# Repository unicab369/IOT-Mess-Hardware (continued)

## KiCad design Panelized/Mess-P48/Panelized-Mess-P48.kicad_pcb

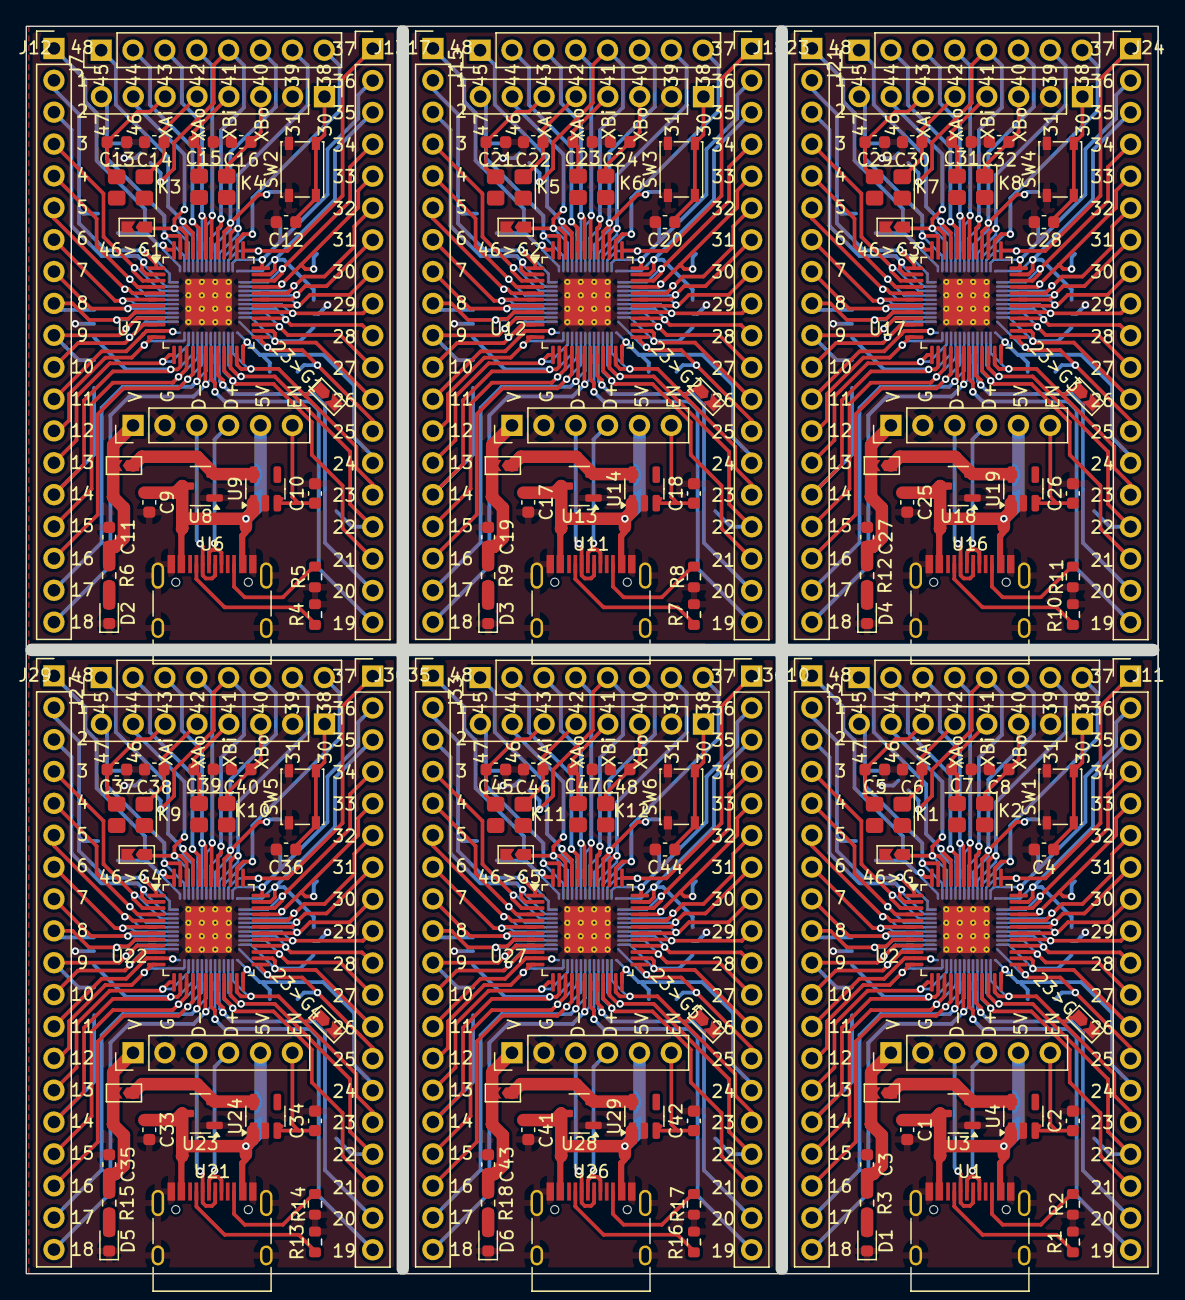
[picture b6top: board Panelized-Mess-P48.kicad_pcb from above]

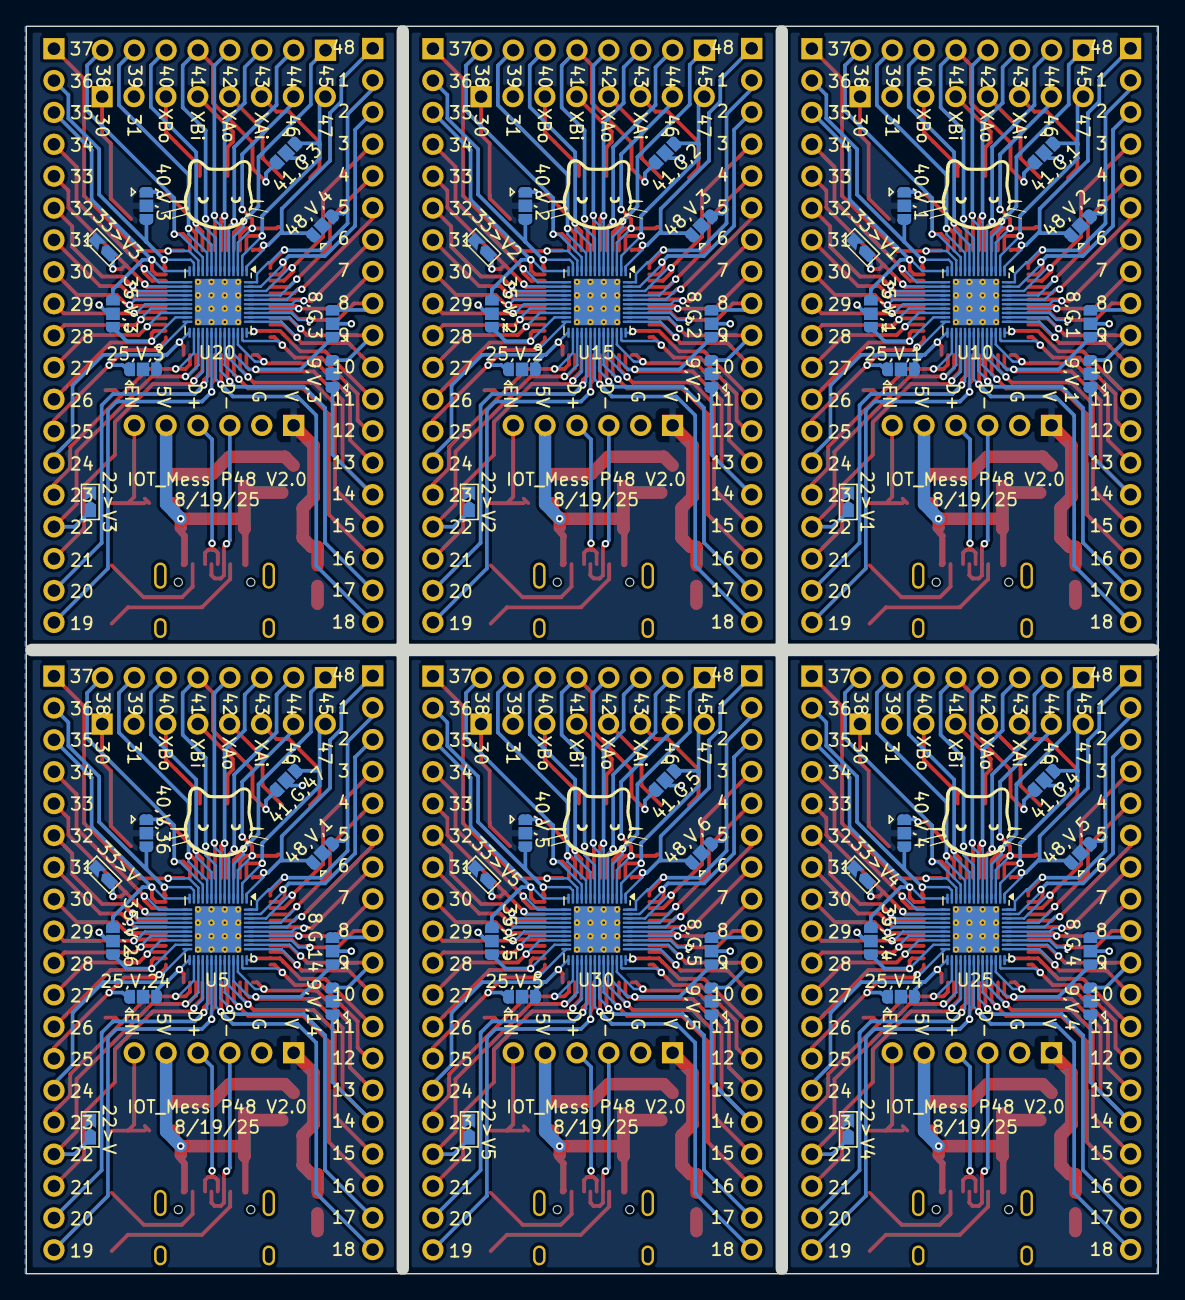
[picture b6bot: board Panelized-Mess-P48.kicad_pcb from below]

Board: 2 copper layers, 90.2 x 99.4 mm, 222 parts (60 on the bottom side), 63 nets.

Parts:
8,G,1, 8,G,2, 8,G,3, 8,G,4, 8,G,5, 8,G,14, 9,V,1, 9,V,2, 9,V,3, 9,V,4, 9,V,5, 9,V,14, 25,V,1, 25,V,2, 25,V,3, 25,V,4, 25,V,5, 25,V,24, 35,V,1, 35,V,2, 35,V,3, 35,V,4, 35,V,5, 35,V,26, 40,V,1, 40,V,2, 40,V,3, 40,V,4, 40,V,5, 40,V,36, 41,G,1, 41,G,2, 41,G,3, 41,G,4, 41,G,5, 41,G,47, 48,V,1, 48,V,2, 48,V,3, 48,V,4, 48,V,5, 48,V,6: Jumper; Jumper-3_P1.3mm_Open_RoundedPad1.0x1.5mm
22>V, 22>V1, 22>V2, 22>V3, 22>V4, 22>V5, 23>G, 23>G1, 23>G2, 23>G3, 23>G4, 23>G5, 33>V, 33>V1, 33>V2, 33>V3, 33>V4, 33>V5, 46>G, 46>G1, 46>G2, 46>G3, 46>G4, 46>G5: Jumper_2; Jumpper-triangle
C1, C9, C17, C25, C33, C41: 10u; C_0603_1608Metric
C2, C3, C10, C11, C18, C19, C26, C27, C34, C35, C42, C43: 1u; C_0603_1608Metric
C4, C12, C20, C28, C36, C44: .1u; C_0603_1608Metric
C5, C6, C13, C14, C21, C22, C29, C30, C37, C38, C45, C46: 15-30pF; C_0603_1608Metric
C7, C8, C15, C16, C23, C24, C31, C32, C39, C40, C47, C48: 12-25pF; C_0603_1608Metric
D1, D2, D3, D4, D5, D6: LED; LED_0603_1608Metric
J1, J5, J9, J19, J25, J31: Jumper_2; Jumpper-triangle
J2, J6, J14, J20, J26, J32: Conn_01x06_Pin; PinHeader_1x06_P2.54mm_Vertical
J3, J4, J7, J8, J15, J16, J21, J22, J27, J28, J33, J34: Conn_01x08_Pin; PinHeader_1x08_P2.54mm_Vertical
J10, J11, J12, J13, J17, J18, J23, J24, J29, J30, J35, J36: Conn_01x19_Pin; PinHeader_1x19_P2.54mm_Vertical
K1, K2, K3, K4, K5, K6, K7, K8, K9, K10, K11, K12: Crystal; Crystal_SMD_3225-4Pin_3.2x2.5mm
R1, R2, R4, R5, R7, R8, R10, R11, R13, R14, R16, R17: 5.1K; R_0603_1608Metric
R3, R6, R9, R12, R15, R18: R; R_0603_1608Metric
SW1, SW2, SW3, SW4, SW5, SW6: SW_Push; SW_SPST_PTS810
U1, U6, U11, U16, U21, U26: USB_C_Receptacle_USB2.0_16P; USB_C_Receptacle_HRO_TYPE-C-31-M-12
U2, U7, U12, U17, U22, U27: LQFP-48-1EP_7x7mm_P0.5mm_EP3.6x3.6mm
U3, U8, U13, U18, U23, U28: XC6206PxxxMR; SOT-23-3
U4, U9, U14, U19, U24, U29: ME6211C33M5; SOT-23-5
U5, U10, U15, U20, U25, U30: CH32L103C8T6; QFN-48-1EP_5x5mm_P0.35mm_EP3.7x3.7mm_ThermalVias

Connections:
5V: C1.1, C9.1, C17.1, C25.1, C33.1, C41.1, J2.5, J6.5, J14.5, J20.5, J26.5, J32.5, U1.A4 (VBUS), U1.A9 (VBUS), U1.B4 (VBUS), U1.B9 (VBUS), U3.3 (VI), U4.1 (V_{IN}), U6.A4 (VBUS), U6.A9 (VBUS), U6.B4 (VBUS), U6.B9 (VBUS), U8.3 (VI), U9.1 (V_{IN}), U11.A4 (VBUS), U11.A9 (VBUS), U11.B4 (VBUS), U11.B9 (VBUS), U13.3 (VI), U14.1 (V_{IN}), U16.A4 (VBUS), U16.A9 (VBUS), U16.B4 (VBUS), U16.B9 (VBUS), U18.3 (VI), U19.1 (V_{IN}), U21.A4 (VBUS), U21.A9 (VBUS), U21.B4 (VBUS), U21.B9 (VBUS), U23.3 (VI), U24.1 (V_{IN}), U26.A4 (VBUS), U26.A9 (VBUS), U26.B4 (VBUS), U26.B9 (VBUS), U28.3 (VI), U29.1 (V_{IN})
D+: J2.4, J6.4, J14.4, J20.4, J26.4, J32.4, U1.A6 (D+), U1.B6 (D+), U6.A6 (D+), U6.B6 (D+), U11.A6 (D+), U11.B6 (D+), U16.A6 (D+), U16.B6 (D+), U21.A6 (D+), U21.B6 (D+), U26.A6 (D+), U26.B6 (D+)
D-: J2.3, J6.3, J14.3, J20.3, J26.3, J32.3, U1.A7 (D-), U1.B7 (D-), U6.A7 (D-), U6.B7 (D-), U11.A7 (D-), U11.B7 (D-), U16.A7 (D-), U16.B7 (D-), U21.A7 (D-), U21.B7 (D-), U26.A7 (D-), U26.B7 (D-)
EN: C2.1, C10.1, C18.1, C26.1, C34.1, C42.1, J2.6, J6.6, J14.6, J20.6, J26.6, J32.6, U4.3 (CE), U9.3 (CE), U14.3 (CE), U19.3 (CE), U24.3 (CE), U29.3 (CE)
GND: 8,G,1.2 (C), 8,G,2.2 (C), 8,G,3.2 (C), 8,G,4.2 (C), 8,G,5.2 (C), 8,G,14.2 (C), 23>G.2 (B), 23>G1.2 (B), 23>G2.2 (B), 23>G3.2 (B), 23>G4.2 (B), 23>G5.2 (B), 35,V,1.2 (C), 35,V,2.2 (C), 35,V,3.2 (C), 35,V,4.2 (C), 35,V,5.2 (C), 35,V,26.2 (C), 41,G,1.2 (C), 41,G,2.2 (C), 41,G,3.2 (C), 41,G,4.2 (C), 41,G,5.2 (C), 41,G,47.2 (C), 46>G.2 (B), 46>G1.2 (B), 46>G2.2 (B), 46>G3.2 (B), 46>G4.2 (B), 46>G5.2 (B), C1.2, C2.2, C3.2, C4.2, C5.2, C6.2, C7.2, C8.2, C9.2, C10.2, C11.2, C12.2, C13.2, C14.2, C15.2, C16.2, C17.2, C18.2, C19.2, C20.2, C21.2, C22.2, C23.2, C24.2, C25.2, C26.2, C27.2, C28.2, C29.2, C30.2, C31.2, C32.2, C33.2, C34.2, C35.2, C36.2, C37.2, C38.2, C39.2, C40.2, C41.2, C42.2, C43.2, C44.2, C45.2, C46.2, C47.2, C48.2, D1.1 (K), D2.1 (K), D3.1 (K), D4.1 (K), D5.1 (K), D6.1 (K), J2.2, J4.2, J6.2, J8.2, J14.2, J16.2, J20.2, J22.2, J26.2, J28.2, J32.2, J34.2, R1.2, R2.2, R4.2, R5.2, R7.2, R8.2, R10.2, R11.2, R13.2, R14.2, R16.2, R17.2, SW1.2, SW2.2, SW3.2, SW4.2, SW5.2, SW6.2, U1.A1 (GND), U1.A12 (GND), U1.B1 (GND), U1.B12 (GND), U1.S1 (SHIELD), U2.49 (VSS), U3.1 (GND), U4.2 (V_{SS}), U5.49 (VSS), U6.A1 (GND), U6.A12 (GND), U6.B1 (GND), U6.B12 (GND), U6.S1 (SHIELD), U7.49 (VSS), U8.1 (GND), U9.2 (V_{SS}), U10.49 (VSS), U11.A1 (GND), U11.A12 (GND), U11.B1 (GND), U11.B12 (GND), U11.S1 (SHIELD), U12.49 (VSS), U13.1 (GND), U14.2 (V_{SS}), U15.49 (VSS), U16.A1 (GND), U16.A12 (GND), U16.B1 (GND), U16.B12 (GND), U16.S1 (SHIELD), U17.49 (VSS), U18.1 (GND), U19.2 (V_{SS}), U20.49 (VSS), U21.A1 (GND), U21.A12 (GND), U21.B1 (GND), U21.B12 (GND), U21.S1 (SHIELD), U22.49 (VSS), U23.1 (GND), U24.2 (V_{SS}), U25.49 (VSS), U26.A1 (GND), U26.A12 (GND), U26.B1 (GND), U26.B12 (GND), U26.S1 (SHIELD), U27.49 (VSS), U28.1 (GND), U29.2 (V_{SS}), U30.49 (VSS)
unnamed: D1.2 (A), D2.2 (A), D3.2 (A), D4.2 (A), D5.2 (A), D6.2 (A), R3.2, R6.2, R9.2, R12.2, R15.2, R18.2
unnamed: J1.1 (A), J5.1 (A), J9.1 (A), J19.1 (A), J25.1 (A), J31.1 (A), U3.2 (VO), U4.5 (V_{OUT}), U8.2 (VO), U9.5 (V_{OUT}), U13.2 (VO), U14.5 (V_{OUT}), U18.2 (VO), U19.5 (V_{OUT}), U23.2 (VO), U24.5 (V_{OUT}), U28.2 (VO), U29.5 (V_{OUT})
unnamed: C4.1, C12.1, C20.1, C28.1, C36.1, C44.1, J4.1, J8.1, J16.1, J22.1, J28.1, J34.1, SW1.1, SW2.1, SW3.1, SW4.1, SW5.1, SW6.1
unnamed: C8.1, C16.1, C24.1, C32.1, C40.1, C48.1, J4.3, J8.3, J16.3, J22.3, J28.3, J34.3, K2.1, K4.1, K6.1, K8.1, K10.1, K12.1
unnamed: C7.1, C15.1, C23.1, C31.1, C39.1, C47.1, J4.4, J8.4, J16.4, J22.4, J28.4, J34.4, K2.2, K4.2, K6.2, K8.2, K10.2, K12.2
unnamed: C6.1, C14.1, C22.1, C30.1, C38.1, C46.1, J4.5, J8.5, J16.5, J22.5, J28.5, J34.5, K1.1, K3.1, K5.1, K7.1, K9.1, K11.1
unnamed: C5.1, C13.1, C21.1, C29.1, C37.1, C45.1, J4.6, J8.6, J16.6, J22.6, J28.6, J34.6, K1.2, K3.2, K5.2, K7.2, K9.2, K11.2
unnamed: R1.1, R4.1, R7.1, R10.1, R13.1, R16.1, U1.A5 (CC1), U6.A5 (CC1), U11.A5 (CC1), U16.A5 (CC1), U21.A5 (CC1), U26.A5 (CC1)
unnamed: R2.1, R5.1, R8.1, R11.1, R14.1, R17.1, U1.B5 (CC2), U6.B5 (CC2), U11.B5 (CC2), U16.B5 (CC2), U21.B5 (CC2), U26.B5 (CC2)
P_1: 48,V,1.3 (B), 48,V,2.3 (B), 48,V,3.3 (B), 48,V,4.3 (B), 48,V,5.3 (B), 48,V,6.3 (B), J10.2, J12.2, J17.2, J23.2, J29.2, J35.2, U2.1 (VBAT), U5.48 (VDD_3), U7.1 (VBAT), U10.48 (VDD_3), U12.1 (VBAT), U15.48 (VDD_3), U17.1 (VBAT), U20.48 (VDD_3), U22.1 (VBAT), U25.48 (VDD_3), U27.1 (VBAT), U30.48 (VDD_3)
P_2: J10.3, J12.3, J17.3, J23.3, J29.3, J35.3, U2.2 (PC13), U5.47 (VSS_3), U7.2 (PC13), U10.47 (VSS_3), U12.2 (PC13), U15.47 (VSS_3), U17.2 (PC13), U20.47 (VSS_3), U22.2 (PC13), U25.47 (VSS_3), U27.2 (PC13), U30.47 (VSS_3)
P_3: J10.4, J12.4, J17.4, J23.4, J29.4, J35.4, U2.3 (PC14/OSC32_IN), U5.46 (PB9), U7.3 (PC14/OSC32_IN), U10.46 (PB9), U12.3 (PC14/OSC32_IN), U15.46 (PB9), U17.3 (PC14/OSC32_IN), U20.46 (PB9), U22.3 (PC14/OSC32_IN), U25.46 (PB9), U27.3 (PC14/OSC32_IN), U30.46 (PB9)
P_4: J10.5, J12.5, J17.5, J23.5, J29.5, J35.5, U2.4 (PC15/OSC32_OUT), U5.45 (PB8), U7.4 (PC15/OSC32_OUT), U10.45 (PB8), U12.4 (PC15/OSC32_OUT), U15.45 (PB8), U17.4 (PC15/OSC32_OUT), U20.45 (PB8), U22.4 (PC15/OSC32_OUT), U25.45 (PB8), U27.4 (PC15/OSC32_OUT), U30.45 (PB8)
P_5: J10.6, J12.6, J17.6, J23.6, J29.6, J35.6, U2.5 (PD0/OSC_IN), U5.44 (BOOT0), U7.5 (PD0/OSC_IN), U10.44 (BOOT0), U12.5 (PD0/OSC_IN), U15.44 (BOOT0), U17.5 (PD0/OSC_IN), U20.44 (BOOT0), U22.5 (PD0/OSC_IN), U25.44 (BOOT0), U27.5 (PD0/OSC_IN), U30.44 (BOOT0)
P_6: J10.7, J12.7, J17.7, J23.7, J29.7, J35.7, U2.6 (PD1/OSC_OUT), U5.43 (PB7/USB2_DP/SDA*), U7.6 (PD1/OSC_OUT), U10.43 (PB7/USB2_DP/SDA*), U12.6 (PD1/OSC_OUT), U15.43 (PB7/USB2_DP/SDA*), U17.6 (PD1/OSC_OUT), U20.43 (PB7/USB2_DP/SDA*), U22.6 (PD1/OSC_OUT), U25.43 (PB7/USB2_DP/SDA*), U27.6 (PD1/OSC_OUT), U30.43 (PB7/USB2_DP/SDA*)
P_7: J10.8, J12.8, J17.8, J23.8, J29.8, J35.8, U2.7 (NRST), U5.42 (PB6/USB2_DM/SCL*), U7.7 (NRST), U10.42 (PB6/USB2_DM/SCL*), U12.7 (NRST), U15.42 (PB6/USB2_DM/SCL*), U17.7 (NRST), U20.42 (PB6/USB2_DM/SCL*), U22.7 (NRST), U25.42 (PB6/USB2_DM/SCL*), U27.7 (NRST), U30.42 (PB6/USB2_DM/SCL*)
P_8: 8,G,1.3 (B), 8,G,2.3 (B), 8,G,3.3 (B), 8,G,4.3 (B), 8,G,5.3 (B), 8,G,14.3 (B), J10.9, J12.9, J17.9, J23.9, J29.9, J35.9, U2.8 (VSSA), U5.41 (PB5), U7.8 (VSSA), U10.41 (PB5), U12.8 (VSSA), U15.41 (PB5), U17.8 (VSSA), U20.41 (PB5), U22.8 (VSSA), U25.41 (PB5), U27.8 (VSSA), U30.41 (PB5)
P_9: 9,V,1.3 (B), 9,V,2.3 (B), 9,V,3.3 (B), 9,V,4.3 (B), 9,V,5.3 (B), 9,V,14.3 (B), J10.10, J12.10, J17.10, J23.10, J29.10, J35.10, U2.9 (VDDA), U5.40 (PB4), U7.9 (VDDA), U10.40 (PB4), U12.9 (VDDA), U15.40 (PB4), U17.9 (VDDA), U20.40 (PB4), U22.9 (VDDA), U25.40 (PB4), U27.9 (VDDA), U30.40 (PB4)
P_10: J10.11, J12.11, J17.11, J23.11, J29.11, J35.11, U2.10 (PA0/ADC0/WKUP), U5.39 (PB3), U7.10 (PA0/ADC0/WKUP), U10.39 (PB3), U12.10 (PA0/ADC0/WKUP), U15.39 (PB3), U17.10 (PA0/ADC0/WKUP), U20.39 (PB3), U22.10 (PA0/ADC0/WKUP), U25.39 (PB3), U27.10 (PA0/ADC0/WKUP), U30.39 (PB3)
P_11: J10.12, J12.12, J17.12, J23.12, J29.12, J35.12, U2.11 (PA1/ADC1), U5.38 (PA15), U7.11 (PA1/ADC1), U10.38 (PA15), U12.11 (PA1/ADC1), U15.38 (PA15), U17.11 (PA1/ADC1), U20.38 (PA15), U22.11 (PA1/ADC1), U25.38 (PA15), U27.11 (PA1/ADC1), U30.38 (PA15)
P_12: J10.13, J12.13, J17.13, J23.13, J29.13, J35.13, U2.12 (PA2/ADC2), U5.37 (PA14/SWCLK), U7.12 (PA2/ADC2), U10.37 (PA14/SWCLK), U12.12 (PA2/ADC2), U15.37 (PA14/SWCLK), U17.12 (PA2/ADC2), U20.37 (PA14/SWCLK), U22.12 (PA2/ADC2), U25.37 (PA14/SWCLK), U27.12 (PA2/ADC2), U30.37 (PA14/SWCLK)
P_13: J10.14, J12.14, J17.14, J23.14, J29.14, J35.14, U2.13 (PA3/ADC3), U5.36 (VDD_2), U7.13 (PA3/ADC3), U10.36 (VDD_2), U12.13 (PA3/ADC3), U15.36 (VDD_2), U17.13 (PA3/ADC3), U20.36 (VDD_2), U22.13 (PA3/ADC3), U25.36 (VDD_2), U27.13 (PA3/ADC3), U30.36 (VDD_2)
P_14: 8,G,1.1 (A), 8,G,2.1 (A), 8,G,3.1 (A), 8,G,4.1 (A), 8,G,5.1 (A), 8,G,14.1 (A), 9,V,1.1 (A), 9,V,2.1 (A), 9,V,3.1 (A), 9,V,4.1 (A), 9,V,5.1 (A), 9,V,14.1 (A), J10.15, J12.15, J17.15, J23.15, J29.15, J35.15, U2.14 (PA4/ADC), U5.35 (VSS_2), U7.14 (PA4/ADC), U10.35 (VSS_2), U12.14 (PA4/ADC), U15.35 (VSS_2), U17.14 (PA4/ADC), U20.35 (VSS_2), U22.14 (PA4/ADC), U25.35 (VSS_2), U27.14 (PA4/ADC), U30.35 (VSS_2)
P_15: J10.16, J12.16, J17.16, J23.16, J29.16, J35.16, U2.15 (PA5/ADC5/SCK*), U5.34 (PA23/SWDIO), U7.15 (PA5/ADC5/SCK*), U10.34 (PA23/SWDIO), U12.15 (PA5/ADC5/SCK*), U15.34 (PA23/SWDIO), U17.15 (PA5/ADC5/SCK*), U20.34 (PA23/SWDIO), U22.15 (PA5/ADC5/SCK*), U25.34 (PA23/SWDIO), U27.15 (PA5/ADC5/SCK*), U30.34 (PA23/SWDIO)
P_16: J10.17, J12.17, J17.17, J23.17, J29.17, J35.17, U2.16 (PA6/ADC6/MISO*), U5.33 (PA12/USB_HDP), U7.16 (PA6/ADC6/MISO*), U10.33 (PA12/USB_HDP), U12.16 (PA6/ADC6/MISO*), U15.33 (PA12/USB_HDP), U17.16 (PA6/ADC6/MISO*), U20.33 (PA12/USB_HDP), U22.16 (PA6/ADC6/MISO*), U25.33 (PA12/USB_HDP), U27.16 (PA6/ADC6/MISO*), U30.33 (PA12/USB_HDP)
P_17: J10.18, J12.18, J17.18, J23.18, J29.18, J35.18, U2.17 (PA7/ADC7/MOSI*), U5.32 (PA11/USB_HDM), U7.17 (PA7/ADC7/MOSI*), U10.32 (PA11/USB_HDM), U12.17 (PA7/ADC7/MOSI*), U15.32 (PA11/USB_HDM), U17.17 (PA7/ADC7/MOSI*), U20.32 (PA11/USB_HDM), U22.17 (PA7/ADC7/MOSI*), U25.32 (PA11/USB_HDM), U27.17 (PA7/ADC7/MOSI*), U30.32 (PA11/USB_HDM)
P_18: J10.19, J12.19, J17.19, J23.19, J29.19, J35.19, U2.18 (PB0/ADC8), U5.31 (PA10), U7.18 (PB0/ADC8), U10.31 (PA10), U12.18 (PB0/ADC8), U15.31 (PA10), U17.18 (PB0/ADC8), U20.31 (PA10), U22.18 (PB0/ADC8), U25.31 (PA10), U27.18 (PB0/ADC8), U30.31 (PA10)
P_19: J11.19, J13.19, J18.19, J24.19, J30.19, J36.19, U2.19 (PB1/ADC9), U5.30 (PA9), U7.19 (PB1/ADC9), U10.30 (PA9), U12.19 (PB1/ADC9), U15.30 (PA9), U17.19 (PB1/ADC9), U20.30 (PA9), U22.19 (PB1/ADC9), U25.30 (PA9), U27.19 (PB1/ADC9), U30.30 (PA9)
P_20: J11.18, J13.18, J18.18, J24.18, J30.18, J36.18, U2.20 (PB2/BOTT), U5.29 (PA8), U7.20 (PB2/BOTT), U10.29 (PA8), U12.20 (PB2/BOTT), U15.29 (PA8), U17.20 (PB2/BOTT), U20.29 (PA8), U22.20 (PB2/BOTT), U25.29 (PA8), U27.20 (PB2/BOTT), U30.29 (PA8)
P_21: J11.17, J13.17, J18.17, J24.17, J30.17, J36.17, U2.21 (PB10/SCL2*), U5.28 (PD15/MOSI_2*), U7.21 (PB10/SCL2*), U10.28 (PD15/MOSI_2*), U12.21 (PB10/SCL2*), U15.28 (PD15/MOSI_2*), U17.21 (PB10/SCL2*), U20.28 (PD15/MOSI_2*), U22.21 (PB10/SCL2*), U25.28 (PD15/MOSI_2*), U27.21 (PB10/SCL2*), U30.28 (PD15/MOSI_2*)
P_22: 22>V.1 (A), 22>V1.1 (A), 22>V2.1 (A), 22>V3.1 (A), 22>V4.1 (A), 22>V5.1 (A), J11.16, J13.16, J18.16, J24.16, J30.16, J36.16, U2.22 (PB11/SDA2*), U5.27 (PD14/MISO_2*), U7.22 (PB11/SDA2*), U10.27 (PD14/MISO_2*), U12.22 (PB11/SDA2*), U15.27 (PD14/MISO_2*), U17.22 (PB11/SDA2*), U20.27 (PD14/MISO_2*), U22.22 (PB11/SDA2*), U25.27 (PD14/MISO_2*), U27.22 (PB11/SDA2*), U30.27 (PD14/MISO_2*)
P_23: 23>G.1 (A), 23>G1.1 (A), 23>G2.1 (A), 23>G3.1 (A), 23>G4.1 (A), 23>G5.1 (A), J11.15, J13.15, J18.15, J24.15, J30.15, J36.15, U2.23 (VSS_1), U5.26 (PD13/SCK_2*), U7.23 (VSS_1), U10.26 (PD13/SCK_2*), U12.23 (VSS_1), U15.26 (PD13/SCK_2*), U17.23 (VSS_1), U20.26 (PD13/SCK_2*), U22.23 (VSS_1), U25.26 (PD13/SCK_2*), U27.23 (VSS_1), U30.26 (PD13/SCK_2*)
P_24: 25,V,1.3 (B), 25,V,2.3 (B), 25,V,3.3 (B), 25,V,4.3 (B), 25,V,5.3 (B), 25,V,24.3 (B), J11.14, J13.14, J18.14, J24.14, J30.14, J36.14, U2.24 (VDD_VIO_1), U5.25 (PD12), U7.24 (VDD_VIO_1), U10.25 (PD12), U12.24 (VDD_VIO_1), U15.25 (PD12), U17.24 (VDD_VIO_1), U20.25 (PD12), U22.24 (VDD_VIO_1), U25.25 (PD12), U27.24 (VDD_VIO_1), U30.25 (PD12)
P_25: 25,V,1.1 (A), 25,V,2.1 (A), 25,V,3.1 (A), 25,V,4.1 (A), 25,V,5.1 (A), 25,V,24.1 (A), J11.13, J13.13, J18.13, J24.13, J30.13, J36.13, U2.25 (PB12), U5.24 (VDD_1), U7.25 (PB12), U10.24 (VDD_1), U12.25 (PB12), U15.24 (VDD_1), U17.25 (PB12), U20.24 (VDD_1), U22.25 (PB12), U25.24 (VDD_1), U27.25 (PB12), U30.24 (VDD_1)
P_26: 35,V,1.1 (A), 35,V,2.1 (A), 35,V,3.1 (A), 35,V,4.1 (A), 35,V,5.1 (A), 35,V,26.1 (A), J11.12, J13.12, J18.12, J24.12, J30.12, J36.12, U2.26 (PB13/SCK2*), U5.23 (VSS_1), U7.26 (PB13/SCK2*), U10.23 (VSS_1), U12.26 (PB13/SCK2*), U15.23 (VSS_1), U17.26 (PB13/SCK2*), U20.23 (VSS_1), U22.26 (PB13/SCK2*), U25.23 (VSS_1), U27.26 (PB13/SCK2*), U30.23 (VSS_1)
P_27: J11.11, J13.11, J18.11, J24.11, J30.11, J36.11, U2.27 (PB14/MISO2*), U5.22 (BP11/SDA2*), U7.27 (PB14/MISO2*), U10.22 (BP11/SDA2*), U12.27 (PB14/MISO2*), U15.22 (BP11/SDA2*), U17.27 (PB14/MISO2*), U20.22 (BP11/SDA2*), U22.27 (PB14/MISO2*), U25.22 (BP11/SDA2*), U27.27 (PB14/MISO2*), U30.22 (BP11/SDA2*)
P_28: J11.10, J13.10, J18.10, J24.10, J30.10, J36.10, U2.28 (PB15/MOSI2*), U5.21 (PB10/SCL2*), U7.28 (PB15/MOSI2*), U10.21 (PB10/SCL2*), U12.28 (PB15/MOSI2*), U15.21 (PB10/SCL2*), U17.28 (PB15/MOSI2*), U20.21 (PB10/SCL2*), U22.28 (PB15/MOSI2*), U25.21 (PB10/SCL2*), U27.28 (PB15/MOSI2*), U30.21 (PB10/SCL2*)
P_29: J11.9, J13.9, J18.9, J24.9, J30.9, J36.9, U2.29 (PA8), U5.20 (PB2/BOOT), U7.29 (PA8), U10.20 (PB2/BOOT), U12.29 (PA8), U15.20 (PB2/BOOT), U17.29 (PA8), U20.20 (PB2/BOOT), U22.29 (PA8), U25.20 (PB2/BOOT), U27.29 (PA8), U30.20 (PB2/BOOT)
P_30: J11.8, J13.8, J18.8, J24.8, J30.8, J36.8, U2.30 (PA9), U5.19 (PB1/ADC9), U7.30 (PA9), U10.19 (PB1/ADC9), U12.30 (PA9), U15.19 (PB1/ADC9), U17.30 (PA9), U20.19 (PB1/ADC9), U22.30 (PA9), U25.19 (PB1/ADC9), U27.30 (PA9), U30.19 (PB1/ADC9)
P_31: J11.7, J13.7, J18.7, J24.7, J30.7, J36.7, U2.31 (PA10), U5.18 (PB0/ADC8), U7.31 (PA10), U10.18 (PB0/ADC8), U12.31 (PA10), U15.18 (PB0/ADC8), U17.31 (PA10), U20.18 (PB0/ADC8), U22.31 (PA10), U25.18 (PB0/ADC8), U27.31 (PA10), U30.18 (PB0/ADC8)
P_32: J11.6, J13.6, J18.6, J24.6, J30.6, J36.6, U2.32 (PA11/USB1_DM), U5.17 (PA7/ADC7/MOSI*), U7.32 (PA11/USB1_DM), U10.17 (PA7/ADC7/MOSI*), U12.32 (PA11/USB1_DM), U15.17 (PA7/ADC7/MOSI*), U17.32 (PA11/USB1_DM), U20.17 (PA7/ADC7/MOSI*), U22.32 (PA11/USB1_DM), U25.17 (PA7/ADC7/MOSI*), U27.32 (PA11/USB1_DM), U30.17 (PA7/ADC7/MOSI*)
P_33: 33>V.1 (A), 33>V1.1 (A), 33>V2.1 (A), 33>V3.1 (A), 33>V4.1 (A), 33>V5.1 (A), J11.5, J13.5, J18.5, J24.5, J30.5, J36.5, U2.33 (PA12/USB1_DP), U5.16 (PA6/ADC6/MISO*), U7.33 (PA12/USB1_DP), U10.16 (PA6/ADC6/MISO*), U12.33 (PA12/USB1_DP), U15.16 (PA6/ADC6/MISO*), U17.33 (PA12/USB1_DP), U20.16 (PA6/ADC6/MISO*), U22.33 (PA12/USB1_DP), U25.16 (PA6/ADC6/MISO*), U27.33 (PA12/USB1_DP), U30.16 (PA6/ADC6/MISO*)
P_34: J11.4, J13.4, J18.4, J24.4, J30.4, J36.4, U2.34 (AP13/SWDIO), U5.15 (PA5/ADC5/ADC1/SCK*), U7.34 (AP13/SWDIO), U10.15 (PA5/ADC5/ADC1/SCK*), U12.34 (AP13/SWDIO), U15.15 (PA5/ADC5/ADC1/SCK*), U17.34 (AP13/SWDIO), U20.15 (PA5/ADC5/ADC1/SCK*), U22.34 (AP13/SWDIO), U25.15 (PA5/ADC5/ADC1/SCK*), U27.34 (AP13/SWDIO), U30.15 (PA5/ADC5/ADC1/SCK*)
P_35: 35,V,1.3 (B), 35,V,2.3 (B), 35,V,3.3 (B), 35,V,4.3 (B), 35,V,5.3 (B), 35,V,26.3 (B), J11.3, J13.3, J18.3, J24.3, J30.3, J36.3, U2.35 (VSS_2), U5.14 (PA4/ADC4/ADC0), U7.35 (VSS_2), U10.14 (PA4/ADC4/ADC0), U12.35 (VSS_2), U15.14 (PA4/ADC4/ADC0), U17.35 (VSS_2), U20.14 (PA4/ADC4/ADC0), U22.35 (VSS_2), U25.14 (PA4/ADC4/ADC0), U27.35 (VSS_2), U30.14 (PA4/ADC4/ADC0)
P_36: 40,V,1.3 (B), 40,V,2.3 (B), 40,V,3.3 (B), 40,V,4.3 (B), 40,V,5.3 (B), 40,V,36.3 (B), J11.2, J13.2, J18.2, J24.2, J30.2, J36.2, U2.36 (VDD_2), U5.13 (PA3/ADC3), U7.36 (VDD_2), U10.13 (PA3/ADC3), U12.36 (VDD_2), U15.13 (PA3/ADC3), U17.36 (VDD_2), U20.13 (PA3/ADC3), U22.36 (VDD_2), U25.13 (PA3/ADC3), U27.36 (VDD_2), U30.13 (PA3/ADC3)
P_37: J11.1, J13.1, J18.1, J24.1, J30.1, J36.1, U2.37 (PA14/SWCLK), U5.12 (PA2/ADC2), U7.37 (PA14/SWCLK), U10.12 (PA2/ADC2), U12.37 (PA14/SWCLK), U15.12 (PA2/ADC2), U17.37 (PA14/SWCLK), U20.12 (PA2/ADC2), U22.37 (PA14/SWCLK), U25.12 (PA2/ADC2), U27.37 (PA14/SWCLK), U30.12 (PA2/ADC2)
P_38: J3.8, J7.8, J15.8, J21.8, J27.8, J33.8, U2.38 (PA15), U5.11 (PA1/ADC1), U7.38 (PA15), U10.11 (PA1/ADC1), U12.38 (PA15), U15.11 (PA1/ADC1), U17.38 (PA15), U20.11 (PA1/ADC1), U22.38 (PA15), U25.11 (PA1/ADC1), U27.38 (PA15), U30.11 (PA1/ADC1)
P_39: J3.7, J7.7, J15.7, J21.7, J27.7, J33.7, U2.39 (PB3), U5.10 (PA0/ADC0/WKUP), U7.39 (PB3), U10.10 (PA0/ADC0/WKUP), U12.39 (PB3), U15.10 (PA0/ADC0/WKUP), U17.39 (PB3), U20.10 (PA0/ADC0/WKUP), U22.39 (PB3), U25.10 (PA0/ADC0/WKUP), U27.39 (PB3), U30.10 (PA0/ADC0/WKUP)
P_40: 40,V,1.1 (A), 40,V,2.1 (A), 40,V,3.1 (A), 40,V,4.1 (A), 40,V,5.1 (A), 40,V,36.1 (A), J3.6, J7.6, J15.6, J21.6, J27.6, J33.6, U2.40 (PB4), U5.9 (VDDA), U7.40 (PB4), U10.9 (VDDA), U12.40 (PB4), U15.9 (VDDA), U17.40 (PB4), U20.9 (VDDA), U22.40 (PB4), U25.9 (VDDA), U27.40 (PB4), U30.9 (VDDA)
P_41: 41,G,1.3 (B), 41,G,2.3 (B), 41,G,3.3 (B), 41,G,4.3 (B), 41,G,5.3 (B), 41,G,47.3 (B), J3.5, J7.5, J15.5, J21.5, J27.5, J33.5, U2.41 (PB5), U5.8 (VSSA), U7.41 (PB5), U10.8 (VSSA), U12.41 (PB5), U15.8 (VSSA), U17.41 (PB5), U20.8 (VSSA), U22.41 (PB5), U25.8 (VSSA), U27.41 (PB5), U30.8 (VSSA)
P_42: J3.4, J7.4, J15.4, J21.4, J27.4, J33.4, U2.42 (PB6/USB2_DM/SCL*), U5.7 (NRST), U7.42 (PB6/USB2_DM/SCL*), U10.7 (NRST), U12.42 (PB6/USB2_DM/SCL*), U15.7 (NRST), U17.42 (PB6/USB2_DM/SCL*), U20.7 (NRST), U22.42 (PB6/USB2_DM/SCL*), U25.7 (NRST), U27.42 (PB6/USB2_DM/SCL*), U30.7 (NRST)
P_43: J3.3, J7.3, J15.3, J21.3, J27.3, J33.3, U2.43 (PB7/USB2_DP/SDA*), U5.6 (PD1/OSC_OUT), U7.43 (PB7/USB2_DP/SDA*), U10.6 (PD1/OSC_OUT), U12.43 (PB7/USB2_DP/SDA*), U15.6 (PD1/OSC_OUT), U17.43 (PB7/USB2_DP/SDA*), U20.6 (PD1/OSC_OUT), U22.43 (PB7/USB2_DP/SDA*), U25.6 (PD1/OSC_OUT), U27.43 (PB7/USB2_DP/SDA*), U30.6 (PD1/OSC_OUT)
P_44: J3.2, J7.2, J15.2, J21.2, J27.2, J33.2, U2.44 (BOOT0), U5.5 (PD0/OSC_IN), U7.44 (BOOT0), U10.5 (PD0/OSC_IN), U12.44 (BOOT0), U15.5 (PD0/OSC_IN), U17.44 (BOOT0), U20.5 (PD0/OSC_IN), U22.44 (BOOT0), U25.5 (PD0/OSC_IN), U27.44 (BOOT0), U30.5 (PD0/OSC_IN)
P_45: J3.1, J7.1, J15.1, J21.1, J27.1, J33.1, U2.45 (PB8), U5.4 (PC15/OSC32_OUT), U7.45 (PB8), U10.4 (PC15/OSC32_OUT), U12.45 (PB8), U15.4 (PC15/OSC32_OUT), U17.45 (PB8), U20.4 (PC15/OSC32_OUT), U22.45 (PB8), U25.4 (PC15/OSC32_OUT), U27.45 (PB8), U30.4 (PC15/OSC32_OUT)
P_46: 46>G.1 (A), 46>G1.1 (A), 46>G2.1 (A), 46>G3.1 (A), 46>G4.1 (A), 46>G5.1 (A), J4.7, J8.7, J16.7, J22.7, J28.7, J34.7, U2.46 (PB9), U5.3 (PC14/OSC32_IN), U7.46 (PB9), U10.3 (PC14/OSC32_IN), U12.46 (PB9), U15.3 (PC14/OSC32_IN), U17.46 (PB9), U20.3 (PC14/OSC32_IN), U22.46 (PB9), U25.3 (PC14/OSC32_IN), U27.46 (PB9), U30.3 (PC14/OSC32_IN)
P_47: 41,G,1.1 (A), 41,G,2.1 (A), 41,G,3.1 (A), 41,G,4.1 (A), 41,G,5.1 (A), 41,G,47.1 (A), J4.8, J8.8, J16.8, J22.8, J28.8, J34.8, U2.47 (VSS_3), U5.2 (PC13), U7.47 (VSS_3), U10.2 (PC13), U12.47 (VSS_3), U15.2 (PC13), U17.47 (VSS_3), U20.2 (PC13), U22.47 (VSS_3), U25.2 (PC13), U27.47 (VSS_3), U30.2 (PC13)
P_48: 48,V,1.1 (A), 48,V,2.1 (A), 48,V,3.1 (A), 48,V,4.1 (A), 48,V,5.1 (A), 48,V,6.1 (A), J10.1, J12.1, J17.1, J23.1, J29.1, J35.1, U2.48 (VDD_VIO_3), U5.1 (VBAT), U7.48 (VDD_VIO_3), U10.1 (VBAT), U12.48 (VDD_VIO_3), U15.1 (VBAT), U17.48 (VDD_VIO_3), U20.1 (VBAT), U22.48 (VDD_VIO_3), U25.1 (VBAT), U27.48 (VDD_VIO_3), U30.1 (VBAT)
VCC: 9,V,1.2 (C), 9,V,2.2 (C), 9,V,3.2 (C), 9,V,4.2 (C), 9,V,5.2 (C), 9,V,14.2 (C), 22>V.2 (B), 22>V1.2 (B), 22>V2.2 (B), 22>V3.2 (B), 22>V4.2 (B), 22>V5.2 (B), 25,V,1.2 (C), 25,V,2.2 (C), 25,V,3.2 (C), 25,V,4.2 (C), 25,V,5.2 (C), 25,V,24.2 (C), 33>V.2 (B), 33>V1.2 (B), 33>V2.2 (B), 33>V3.2 (B), 33>V4.2 (B), 33>V5.2 (B), 40,V,1.2 (C), 40,V,2.2 (C), 40,V,3.2 (C), 40,V,4.2 (C), 40,V,5.2 (C), 40,V,36.2 (C), 48,V,1.2 (C), 48,V,2.2 (C), 48,V,3.2 (C), 48,V,4.2 (C), 48,V,5.2 (C), 48,V,6.2 (C), C3.1, C11.1, C19.1, C27.1, C35.1, C43.1, J1.2 (B), J2.1, J5.2 (B), J6.1, J9.2 (B), J14.1, J19.2 (B), J20.1, J25.2 (B), J26.1, J31.2 (B), J32.1, R3.1, R6.1, R9.1, R12.1, R15.1, R18.1
